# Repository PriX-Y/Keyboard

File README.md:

# Befor. Im from Poland and im dont speak english very well , dont rate grammer :)

# HI. there is my keyboard
I made this becuse i need keyboard. my actualy keyboard is 12 years: cosaco keyboard what i need use hot glue to repeir what.

it still work but Bro . you see how this look , i dont say its bad keyboard for me is fine but i wanna make something own what i be use for next years.

# So there is my PKSBoard ( i dont have idea for name) 

**Note** im finnaly dont use case becuse i dont have budget left for printing legion

**It base on most simple things but becuse i wanna clean 65%+ i need to make Mcu and Key PCB separate**
 on key pcb you dont see rp2040 its becuse i separte it and is why pick 2.54mm right angle , cable, 

-**MCU:** RP2040-Plus ,  Everyone know wha t mcu is this.

-**PCB:** My own project , Is **65%** size keyboard but i add Function button and Rotery Encoder

old version

-**Switch:** Akko V3 creamy blue is one of best budget switch on the world. its tactical so is silent 
but you fell click

-**Keycaps.** any random chepest keycaps what i can find to fit in budget

-**Stablizators:** for keycaps

-**cable** just cable
there is cart

-**Diods:** i pick that becuse i have footprint only for this one

-**Connector:** to conect it its why is right angle
there is cart from tme

**Case:** is simple case what i made in Fusion , im not skilled in this so is why is a simple.

# **i use programs:**

**Kicad:** For PCB
**Autodesk** fusion: For 3D modeling
**Paint:** for diagram
**Google Docs:** For BOM
**Cursor:** for code

is all i spend aorund 20h on buldi this becuse i spend aorund 7h mcu what i finnaly dont buldi becuse cost. i have all in blueprint site so is why i dont have jounary here. finally my keyboard for me personal is good ( i be happy if it get aproved) 

# btw im pass this 

# there is one thing what left: BOM ( without link there, link verison is in folder)

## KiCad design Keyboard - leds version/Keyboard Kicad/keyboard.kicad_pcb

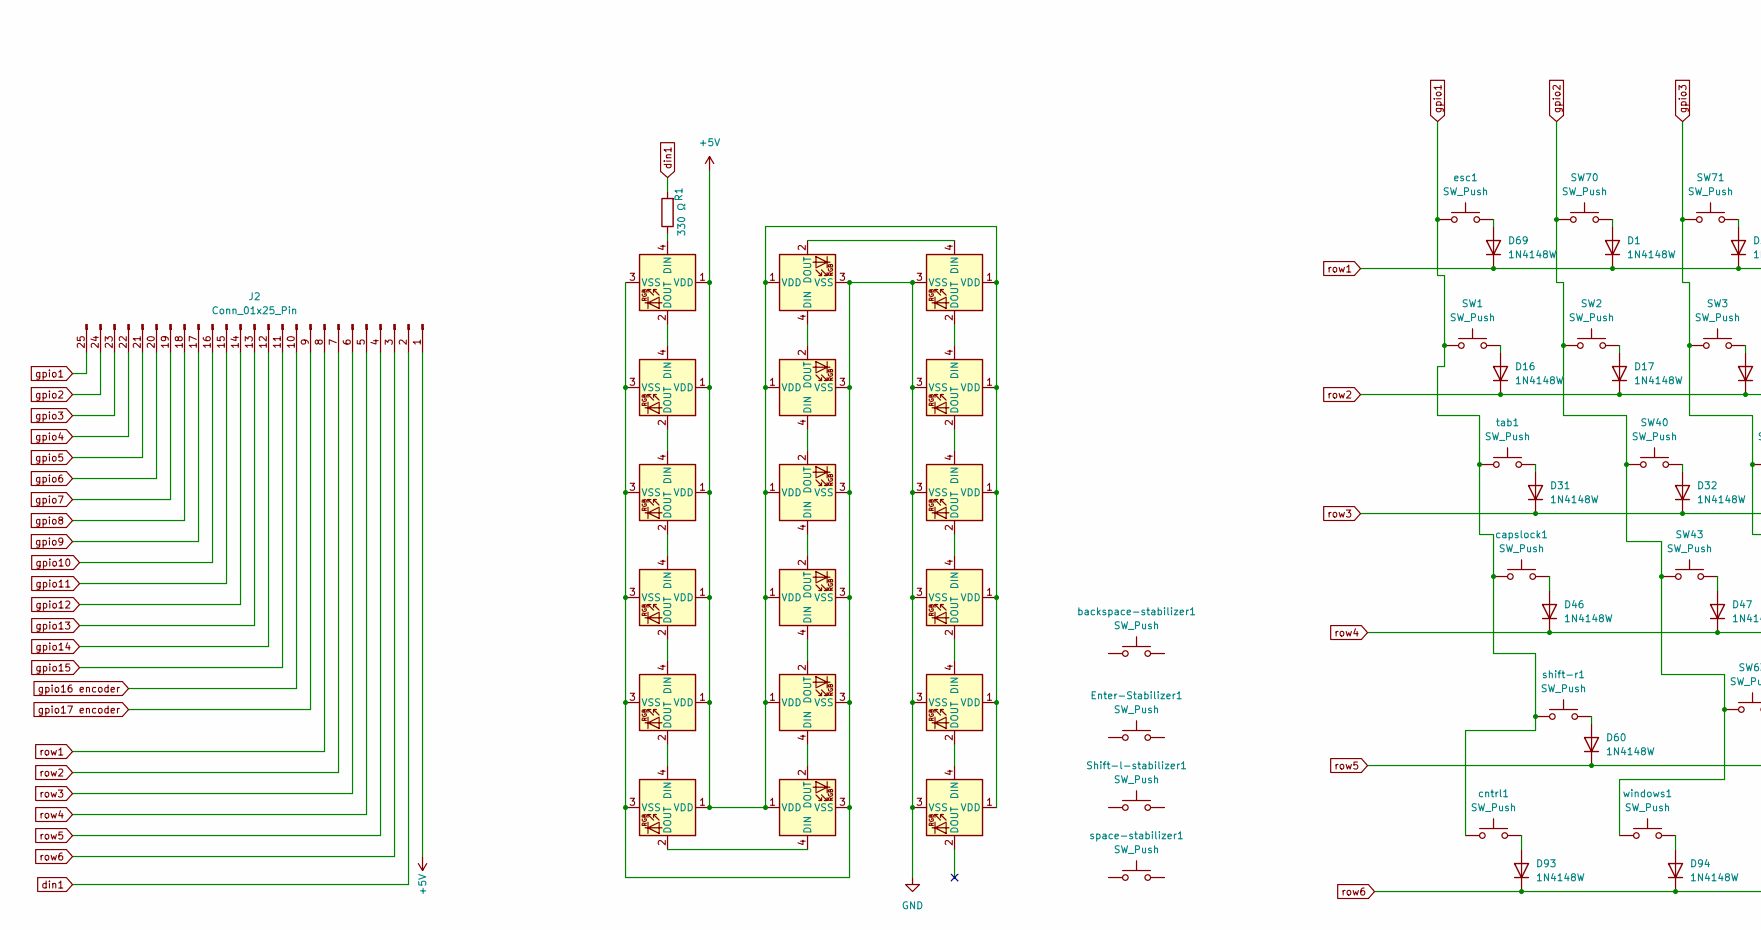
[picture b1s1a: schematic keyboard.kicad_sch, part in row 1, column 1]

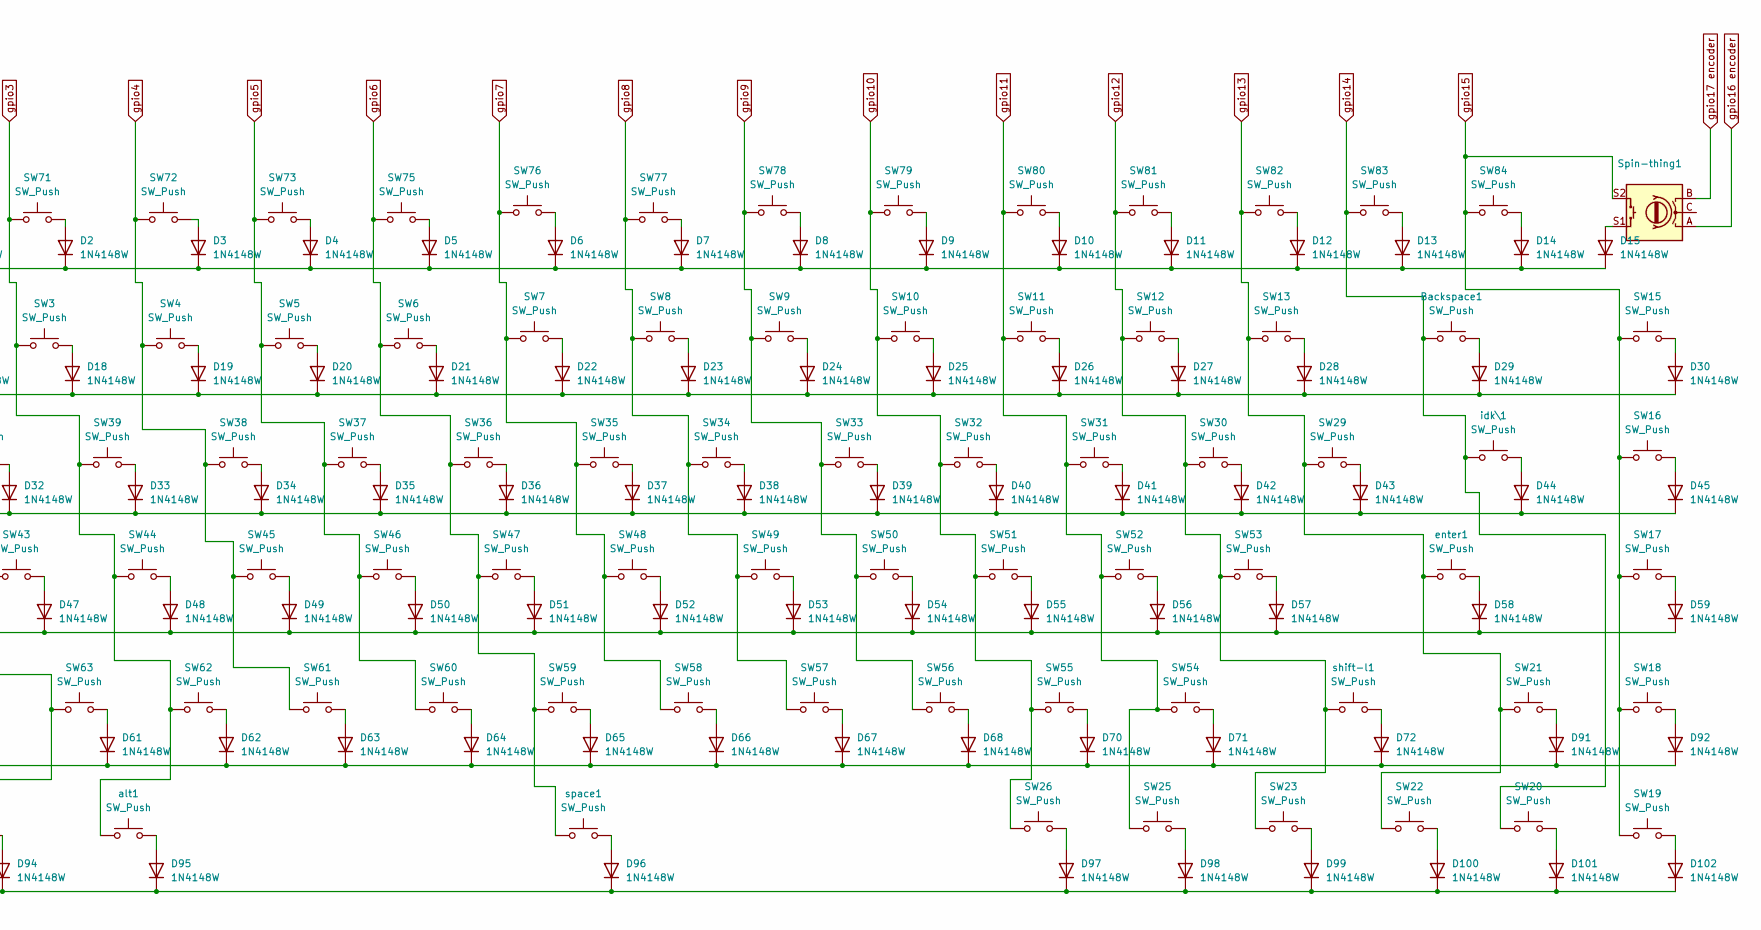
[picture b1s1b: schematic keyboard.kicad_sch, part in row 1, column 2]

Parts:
Backspace1: SW_Push; SW_Cherry_MX_PCB_2.00u
D1, D2, D3, D4, D5, D6, D7, D8, D9, D10, D11, D12, D13, D14, D15, D16, D17, D18, D19, D20, D21, D22, D23, D24, D25, D26, D27, D28, D29, D30, D31, D32, D33, D34, D35, D36, D37, D38, D39, D40, D41, D42, D43, D44, D45, D46, D47, D48, D49, D50, D51, D52, D53, D54, D55, D56, D57, D58, D59, D60, D61, D62, D63, D64, D65, D66, D67, D68, D69, D70, D71, D72, D91, D92, D93, D94, D95, D96, D97, D98, D99, D100, D101, D102: 1N4148W; D_SOD-123
D73, D74, D75, D76, D77, D78, D79, D80, D81, D82, D83, D84, D85, D86, D87, D88, D89, D90: WS2812B; LED_WS2812B-Mini_PLCC4_3.5x3.5mm
Enter-Stabilizer1: SW_Push; Stabilizer_Cherry_MX_2.00u
J2: Conn_01x25_Pin; PinHeader_1x25_P1.00mm_Vertical
R1: 330 Ω; R_0805_2012Metric_Pad1.20x1.40mm_HandSolder
SW1, SW2, SW3, SW4, SW5, SW6, SW7, SW8, SW9, SW10, SW11, SW12, SW13, SW15, SW16, SW17, SW18, SW19, SW20, SW21, SW22, SW23, SW25, SW26, SW29, SW30, SW31, SW32, SW33, SW34, SW35, SW36, SW37, SW38, SW39, SW40, SW43, SW44, SW45, SW46, SW47, SW48, SW49, SW50, SW51, SW52, SW53, SW54, SW55, SW56, SW57, SW58, SW59, SW60, SW61, SW62, SW63, SW70, SW71, SW72, SW73, SW75, SW76, SW77, SW78, SW79, SW80, SW81, SW82, SW83, SW84: SW_Push; SW_Cherry_MX_PCB_1.00u
Shift-l-stabilizer1: SW_Push; Stabilizer_Cherry_MX_2.00u
Spin-thing1: RotaryEncoder_Switch; RotaryEncoder_Alps_EC11E-Switch_Vertical_H20mm_MountingHoles
alt1: SW_Push; SW_Cherry_MX_PCB_1.25u
backspace-stabilizer1: SW_Push; Stabilizer_Cherry_MX_2.00u
capslock1: SW_Push; SW_Cherry_MX_PCB_1.75u
cntrl1: SW_Push; SW_Cherry_MX_PCB_1.25u
enter1: SW_Push; SW_Cherry_MX_PCB_2.00u
esc1: SW_Push; SW_Cherry_MX_PCB_1.00u
idk\1: SW_Push; SW_Cherry_MX_PCB_1.50u
shift-l1: SW_Push; SW_Cherry_MX_PCB_1.75u
shift-r1: SW_Push; SW_Cherry_MX_PCB_2.25u
space1: SW_Push; SW_Cherry_MX_PCB_6.25u
space-stabilizer1: SW_Push; Stabilizer_Cherry_MX_6.25u
tab1: SW_Push; SW_Cherry_MX_PCB_1.50u
windows1: SW_Push; SW_Cherry_MX_PCB_1.25u

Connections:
+5V: D73.1 (VDD), D74.1 (VDD), D75.1 (VDD), D76.1 (VDD), D77.1 (VDD), D78.1 (VDD), D79.1 (VDD), D80.1 (VDD), D81.1 (VDD), D82.1 (VDD), D83.1 (VDD), D84.1 (VDD), D85.1 (VDD), D86.1 (VDD), D87.1 (VDD), D88.1 (VDD), D89.1 (VDD), D90.1 (VDD), J2.1
GND: D73.3 (VSS), D74.3 (VSS), D75.3 (VSS), D76.3 (VSS), D77.3 (VSS), D78.3 (VSS), D79.3 (VSS), D80.3 (VSS), D81.3 (VSS), D82.3 (VSS), D83.3 (VSS), D84.3 (VSS), D85.3 (VSS), D86.3 (VSS), D87.3 (VSS), D88.3 (VSS), D89.3 (VSS), D90.3 (VSS)
unnamed: D1.2 (A), SW70.2
unnamed: D2.2 (A), SW71.2
unnamed: D3.2 (A), SW72.2
unnamed: D4.2 (A), SW73.2
unnamed: D5.2 (A), SW75.2
unnamed: D6.2 (A), SW76.2
unnamed: D7.2 (A), SW77.2
unnamed: D8.2 (A), SW78.2
unnamed: D9.2 (A), SW79.2
unnamed: D10.2 (A), SW80.2
unnamed: D11.2 (A), SW81.2
unnamed: D12.2 (A), SW82.2
unnamed: D13.2 (A), SW83.2
unnamed: D14.2 (A), SW84.2
unnamed: D15.2 (A), Spin-thing1.S1
unnamed: D16.2 (A), SW1.2
unnamed: D17.2 (A), SW2.2
unnamed: D18.2 (A), SW3.2
unnamed: D19.2 (A), SW4.2
unnamed: D20.2 (A), SW5.2
unnamed: D21.2 (A), SW6.2
unnamed: D22.2 (A), SW7.2
unnamed: D23.2 (A), SW8.2
unnamed: D24.2 (A), SW9.2
unnamed: D25.2 (A), SW10.2
unnamed: D26.2 (A), SW11.2
unnamed: D27.2 (A), SW12.2
unnamed: D28.2 (A), SW13.2
unnamed: Backspace1.2, D29.2 (A)
unnamed: D30.2 (A), SW15.2
unnamed: D31.2 (A), tab1.2
unnamed: D32.2 (A), SW40.2
unnamed: D33.2 (A), SW39.2
unnamed: D34.2 (A), SW38.2
unnamed: D35.2 (A), SW37.2
unnamed: D36.2 (A), SW36.2
unnamed: D37.2 (A), SW35.2
unnamed: D38.2 (A), SW34.2
unnamed: D39.2 (A), SW33.2
unnamed: D40.2 (A), SW32.2
unnamed: D41.2 (A), SW31.2
unnamed: D42.2 (A), SW30.2
unnamed: D43.2 (A), SW29.2
unnamed: D44.2 (A), idk\1.2
unnamed: D45.2 (A), SW16.2
unnamed: D46.2 (A), capslock1.2
unnamed: D47.2 (A), SW43.2
unnamed: D48.2 (A), SW44.2
unnamed: D49.2 (A), SW45.2
unnamed: D50.2 (A), SW46.2
unnamed: D51.2 (A), SW47.2
unnamed: D52.2 (A), SW48.2
unnamed: D53.2 (A), SW49.2
unnamed: D54.2 (A), SW50.2
unnamed: D55.2 (A), SW51.2
unnamed: D56.2 (A), SW52.2
unnamed: D57.2 (A), SW53.2
unnamed: D58.2 (A), enter1.2
unnamed: D59.2 (A), SW17.2
unnamed: D60.2 (A), shift-r1.2
unnamed: D61.2 (A), SW63.2
unnamed: D62.2 (A), SW62.2
unnamed: D63.2 (A), SW61.2
unnamed: D64.2 (A), SW60.2
unnamed: D65.2 (A), SW59.2
unnamed: D66.2 (A), SW58.2
unnamed: D67.2 (A), SW57.2
unnamed: D68.2 (A), SW56.2
unnamed: D69.2 (A), esc1.2
unnamed: D70.2 (A), SW55.2
unnamed: D71.2 (A), SW54.2
unnamed: D72.2 (A), shift-l1.2
unnamed: D73.4 (DIN), R1.1
unnamed: D73.2 (DOUT), D74.4 (DIN)
unnamed: D74.2 (DOUT), D75.4 (DIN)
unnamed: D75.2 (DOUT), D76.4 (DIN)
unnamed: D76.2 (DOUT), D77.4 (DIN)
unnamed: D77.2 (DOUT), D78.4 (DIN)
unnamed: D78.2 (DOUT), D79.4 (DIN)
unnamed: D79.2 (DOUT), D80.4 (DIN)
unnamed: D80.2 (DOUT), D81.4 (DIN)
unnamed: D81.2 (DOUT), D82.4 (DIN)
unnamed: D82.2 (DOUT), D83.4 (DIN)
unnamed: D83.2 (DOUT), D84.4 (DIN)
unnamed: D84.2 (DOUT), D90.4 (DIN)
unnamed: D85.4 (DIN), D86.2 (DOUT)
unnamed: D86.4 (DIN), D87.2 (DOUT)
unnamed: D87.4 (DIN), D88.2 (DOUT)
unnamed: D88.4 (DIN), D89.2 (DOUT)
unnamed: D89.4 (DIN), D90.2 (DOUT)
unnamed: D91.2 (A), SW21.2
unnamed: D92.2 (A), SW18.2
unnamed: D93.2 (A), cntrl1.2
unnamed: D94.2 (A), windows1.2
unnamed: D95.2 (A), alt1.2
unnamed: D96.2 (A), space1.2
unnamed: D97.2 (A), SW26.2
unnamed: D98.2 (A), SW25.2
unnamed: D99.2 (A), SW23.2
unnamed: D100.2 (A), SW22.2
unnamed: D101.2 (A), SW20.2
unnamed: D102.2 (A), SW19.2
din1: J2.2, R1.2
gpio1: J2.25, SW1.1, capslock1.1, cntrl1.1, esc1.1, shift-r1.1, tab1.1
gpio2: J2.24, SW2.1, SW40.1, SW43.1, SW63.1, SW70.1, windows1.1
gpio3: J2.23, SW3.1, SW39.1, SW44.1, SW62.1, SW71.1, alt1.1
gpio4: J2.22, SW4.1, SW38.1, SW45.1, SW61.1, SW72.1
gpio5: J2.21, SW5.1, SW37.1, SW46.1, SW60.1, SW73.1
gpio6: J2.20, SW6.1, SW36.1, SW47.1, SW59.1, SW75.1, space1.1
gpio7: J2.19, SW7.1, SW35.1, SW48.1, SW58.1, SW76.1
gpio8: J2.18, SW8.1, SW34.1, SW49.1, SW57.1, SW77.1
gpio9: J2.17, SW9.1, SW33.1, SW50.1, SW56.1, SW78.1
gpio10: J2.16, SW10.1, SW26.1, SW32.1, SW51.1, SW55.1, SW79.1
gpio11: J2.15, SW11.1, SW25.1, SW31.1, SW52.1, SW54.1, SW80.1
gpio12: J2.14, SW12.1, SW23.1, SW30.1, SW53.1, SW81.1, shift-l1.1
gpio13: J2.13, SW13.1, SW21.1, SW22.1, SW29.1, SW82.1, enter1.1
gpio14: Backspace1.1, J2.12, SW20.1, SW83.1, idk\1.1
gpio15: J2.11, SW15.1, SW16.1, SW17.1, SW18.1, SW19.1, SW84.1, Spin-thing1.S2
gpio16 encoder: J2.10, Spin-thing1.A
gpio17 encoder: J2.9, Spin-thing1.B
row1: D1.1 (K), D2.1 (K), D3.1 (K), D4.1 (K), D5.1 (K), D6.1 (K), D7.1 (K), D8.1 (K), D9.1 (K), D10.1 (K), D11.1 (K), D12.1 (K), D13.1 (K), D14.1 (K), D15.1 (K), D69.1 (K), J2.8
row2: D16.1 (K), D17.1 (K), D18.1 (K), D19.1 (K), D20.1 (K), D21.1 (K), D22.1 (K), D23.1 (K), D24.1 (K), D25.1 (K), D26.1 (K), D27.1 (K), D28.1 (K), D29.1 (K), D30.1 (K), J2.7
row3: D31.1 (K), D32.1 (K), D33.1 (K), D34.1 (K), D35.1 (K), D36.1 (K), D37.1 (K), D38.1 (K), D39.1 (K), D40.1 (K), D41.1 (K), D42.1 (K), D43.1 (K), D44.1 (K), D45.1 (K), J2.6
row4: D46.1 (K), D47.1 (K), D48.1 (K), D49.1 (K), D50.1 (K), D51.1 (K), D52.1 (K), D53.1 (K), D54.1 (K), D55.1 (K), D56.1 (K), D57.1 (K), D58.1 (K), D59.1 (K), J2.5
row5: D60.1 (K), D61.1 (K), D62.1 (K), D63.1 (K), D64.1 (K), D65.1 (K), D66.1 (K), D67.1 (K), D68.1 (K), D70.1 (K), D71.1 (K), D72.1 (K), D91.1 (K), D92.1 (K), J2.4
row6: D93.1 (K), D94.1 (K), D95.1 (K), D96.1 (K), D97.1 (K), D98.1 (K), D99.1 (K), D100.1 (K), D101.1 (K), D102.1 (K), J2.3

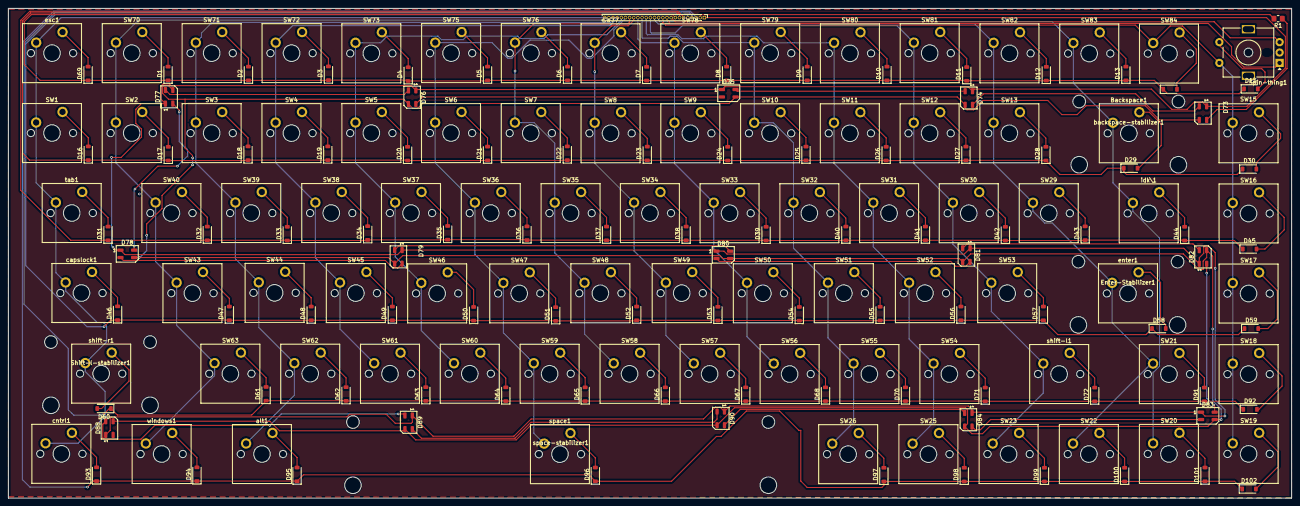
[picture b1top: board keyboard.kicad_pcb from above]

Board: 2 copper layers, 308.9 x 117.9 mm, 189 parts (0 on the bottom side), 125 nets.

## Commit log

2026-03-14 Add greeting to Readme
2026-03-26 Rename Readme to README.md
2026-03-26 Revise README for grammar and clarity
    Corrected typos and improved clarity in the README.
2026-03-26 Enhance README formatting and include images
    Updated README.md to improve formatting and add images.
2026-03-26 Fix typos and enhance README content
    Correct typos and improve clarity in the README.
2026-03-27 Update README with images and MCU information
    Added additional images and clarified MCU description.
2026-05-29 Fix typos and improve clarity in README.md
    Corrected spelling and grammar in the README.
